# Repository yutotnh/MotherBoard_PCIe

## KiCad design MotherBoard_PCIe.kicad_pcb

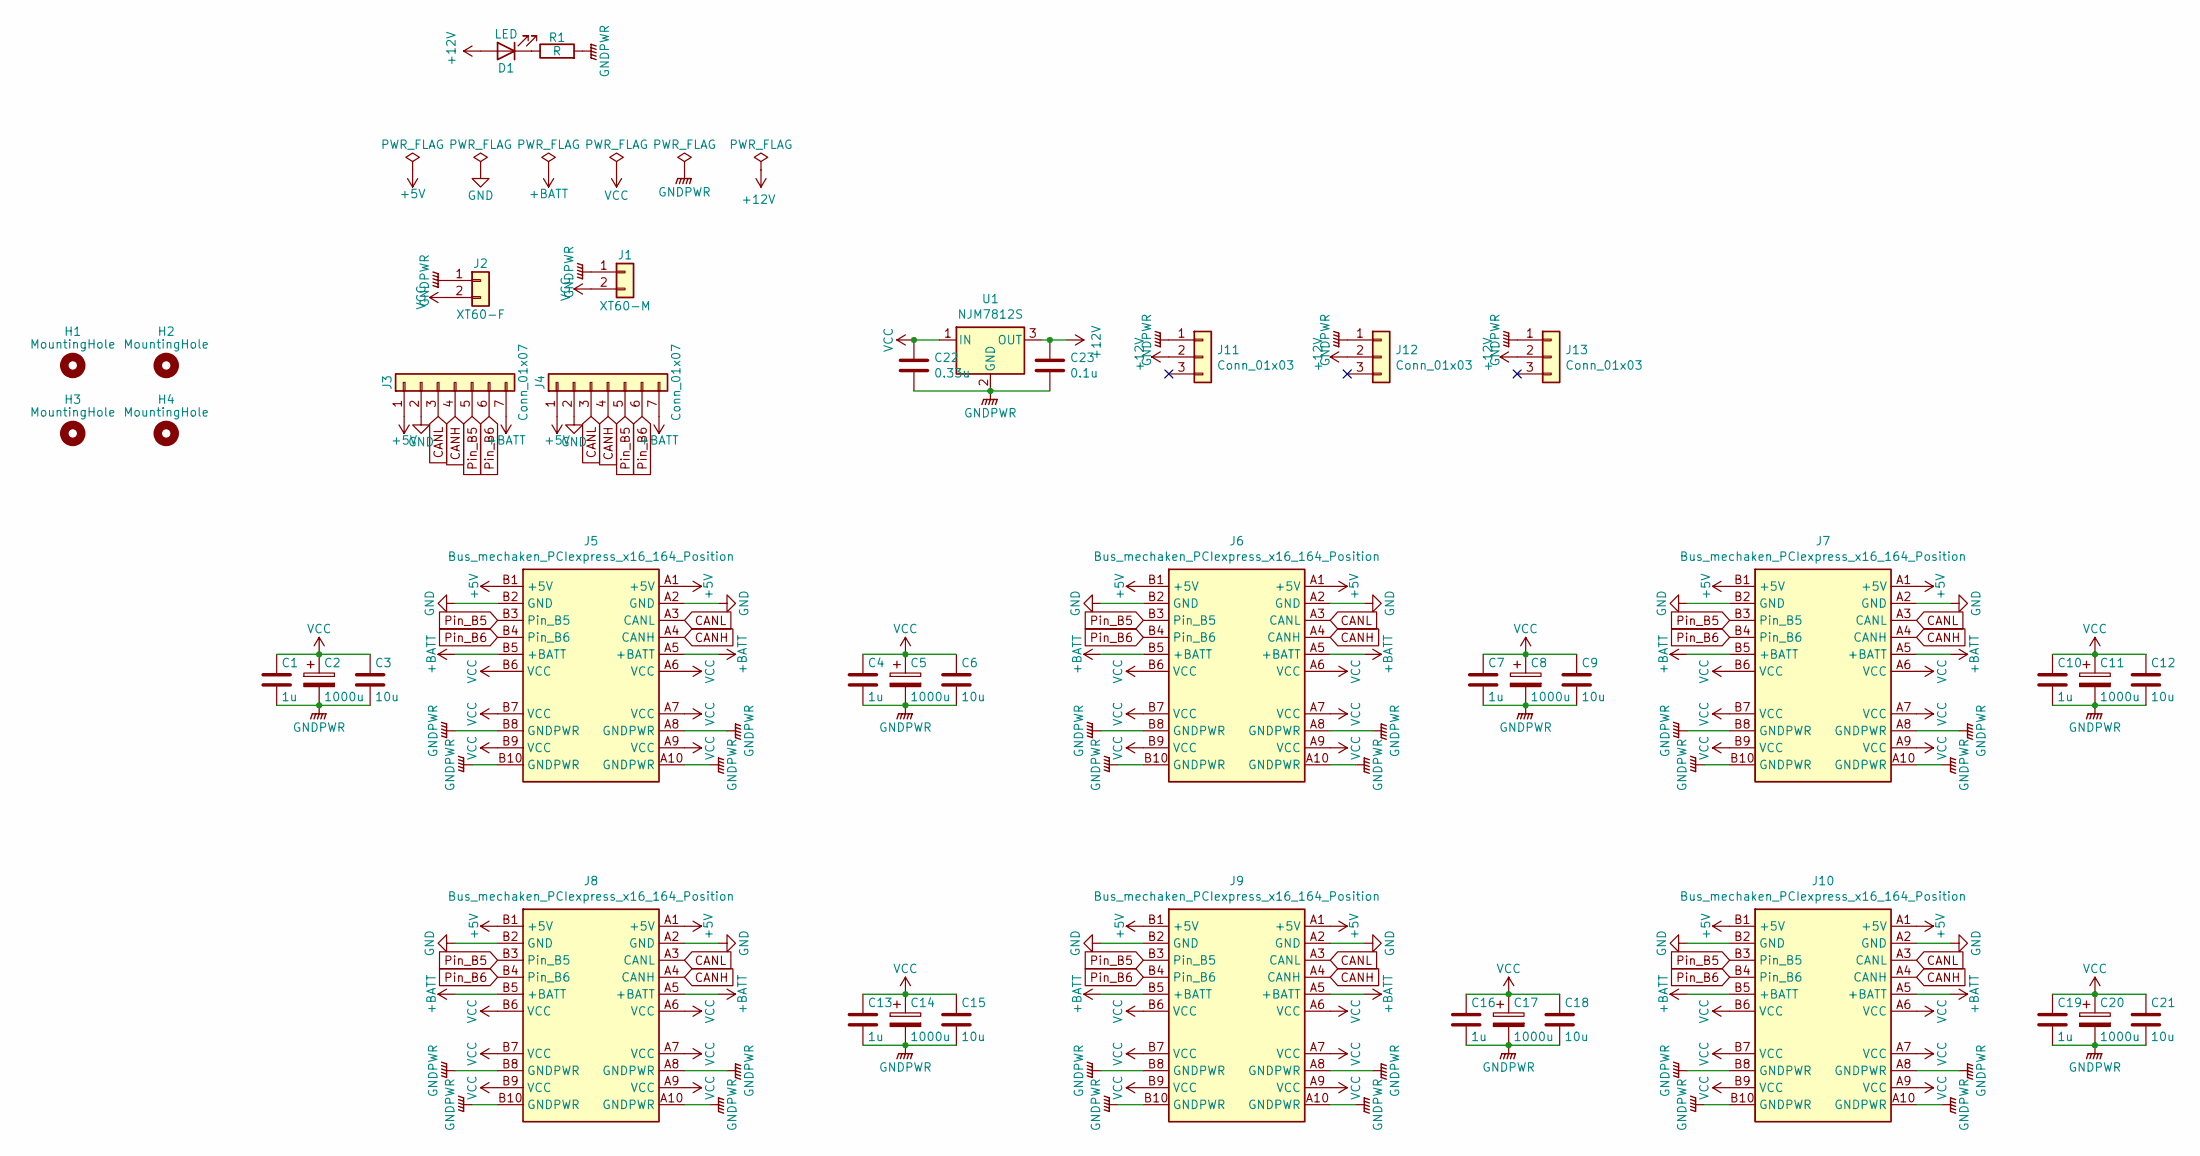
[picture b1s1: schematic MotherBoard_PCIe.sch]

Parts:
C1, C4, C7, C10, C13, C16, C19: 1u; C_0805_2012Metric
C2, C5, C8, C11, C14, C17, C20: 1000u; CP_Radial_D12.5mm_P5.00mm
C3, C6, C9, C12, C15, C18, C21: 10u; C_0805_2012Metric
C22: 0.33u; C_0805_2012Metric
C23: 0.1u; C_0805_2012Metric
D1: LED; LED_D4.0mm
H1, H2, H3, H4: MountingHole; MountingHole_3.2mm_M3
J1: XT60-M; AMASS_XT60-M_1x02_P7.20mm_Vertical
J2: XT60-F; AMASS_XT60-F_1x02_P7.20mm_Vertical
J3, J4: Conn_01x07; PinHeader_1x07_P2.54mm_Vertical
J5, J6, J7, J8, J9, J10: Bus_mechaken_PCIexpress_x16_164_Position; Socket_mechaken_PCIexpress_x16_164_position
J11, J12, J13: Conn_01x03; FanPinHeader_1x03_P2.54mm_Vertical
R1: R; R_0603_1608Metric_Pad1.05x0.95mm_HandSolder
U1: NJM7812S; TO-252-2

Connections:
+5V: J3.1, J4.1, J5.A1 (+5V), J5.B1 (+5V), J6.A1 (+5V), J6.B1 (+5V), J7.A1 (+5V), J7.B1 (+5V), J8.A1 (+5V), J8.B1 (+5V), J9.A1 (+5V), J9.B1 (+5V), J10.A1 (+5V), J10.B1 (+5V)
+12V: C23.1, D1.2 (A), J11.2, J12.2, J13.2, U1.3 (OUT)
+BATT: J3.7, J4.7, J5.A5 (+BATT), J5.B5 (+BATT), J6.A5 (+BATT), J6.B5 (+BATT), J7.A5 (+BATT), J7.B5 (+BATT), J8.A5 (+BATT), J8.B5 (+BATT), J9.A5 (+BATT), J9.B5 (+BATT), J10.A5 (+BATT), J10.B5 (+BATT)
CANH: J3.4, J4.4, J5.A4 (CANH), J6.A4 (CANH), J7.A4 (CANH), J8.A4 (CANH), J9.A4 (CANH), J10.A4 (CANH)
CANL: J3.3, J4.3, J5.A3 (CANL), J6.A3 (CANL), J7.A3 (CANL), J8.A3 (CANL), J9.A3 (CANL), J10.A3 (CANL)
GND: J3.2, J4.2, J5.A2 (GND), J5.B2 (GND), J6.A2 (GND), J6.B2 (GND), J7.A2 (GND), J7.B2 (GND), J8.A2 (GND), J8.B2 (GND), J9.A2 (GND), J9.B2 (GND), J10.A2 (GND), J10.B2 (GND)
GNDPWR: C1.2, C2.2, C3.2, C4.2, C5.2, C6.2, C7.2, C8.2, C9.2, C10.2, C11.2, C12.2, C13.2, C14.2, C15.2, C16.2, C17.2, C18.2, C19.2, C20.2, C21.2, C22.2, C23.2, J1.1, J2.1, J5.A8 (GNDPWR), J5.A10 (GNDPWR), J5.B8 (GNDPWR), J5.B10 (GNDPWR), J6.A8 (GNDPWR), J6.A10 (GNDPWR), J6.B8 (GNDPWR), J6.B10 (GNDPWR), J7.A8 (GNDPWR), J7.A10 (GNDPWR), J7.B8 (GNDPWR), J7.B10 (GNDPWR), J8.A8 (GNDPWR), J8.A10 (GNDPWR), J8.B8 (GNDPWR), J8.B10 (GNDPWR), J9.A8 (GNDPWR), J9.A10 (GNDPWR), J9.B8 (GNDPWR), J9.B10 (GNDPWR), J10.A8 (GNDPWR), J10.A10 (GNDPWR), J10.B8 (GNDPWR), J10.B10 (GNDPWR), J11.1, J12.1, J13.1, R1.2, U1.2 (GND)
unnamed: D1.1 (K), R1.1
Pin_B5: J3.5, J4.5, J5.B3 (Pin_B5), J6.B3 (Pin_B5), J7.B3 (Pin_B5), J8.B3 (Pin_B5), J9.B3 (Pin_B5), J10.B3 (Pin_B5)
Pin_B6: J3.6, J4.6, J5.B4 (Pin_B6), J6.B4 (Pin_B6), J7.B4 (Pin_B6), J8.B4 (Pin_B6), J9.B4 (Pin_B6), J10.B4 (Pin_B6)
VCC: C1.1, C2.1, C3.1, C4.1, C5.1, C6.1, C7.1, C8.1, C9.1, C10.1, C11.1, C12.1, C13.1, C14.1, C15.1, C16.1, C17.1, C18.1, C19.1, C20.1, C21.1, C22.1, J1.2, J2.2, J5.A6 (VCC), J5.A7 (VCC), J5.A9 (VCC), J5.B6 (VCC), J5.B7 (VCC), J5.B9 (VCC), J6.A6 (VCC), J6.A7 (VCC), J6.A9 (VCC), J6.B6 (VCC), J6.B7 (VCC), J6.B9 (VCC), J7.A6 (VCC), J7.A7 (VCC), J7.A9 (VCC), J7.B6 (VCC), J7.B7 (VCC), J7.B9 (VCC), J8.A6 (VCC), J8.A7 (VCC), J8.A9 (VCC), J8.B6 (VCC), J8.B7 (VCC), J8.B9 (VCC), J9.A6 (VCC), J9.A7 (VCC), J9.A9 (VCC), J9.B6 (VCC), J9.B7 (VCC), J9.B9 (VCC), J10.A6 (VCC), J10.A7 (VCC), J10.A9 (VCC), J10.B6 (VCC), J10.B7 (VCC), J10.B9 (VCC), U1.1 (IN)

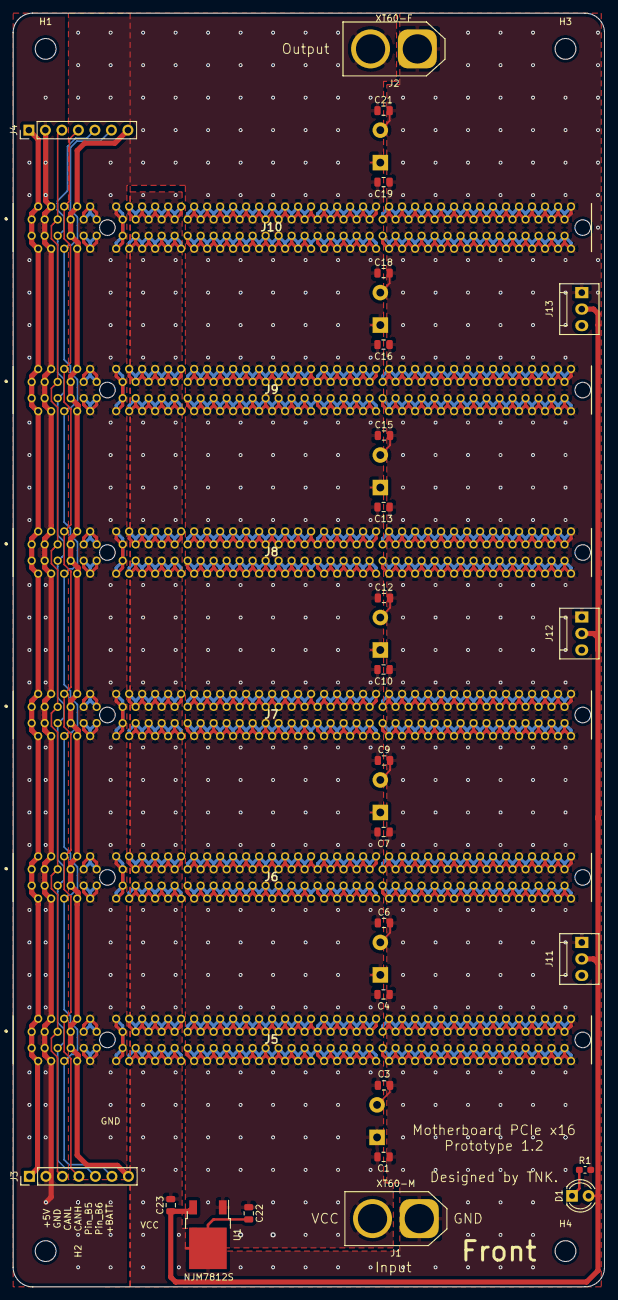
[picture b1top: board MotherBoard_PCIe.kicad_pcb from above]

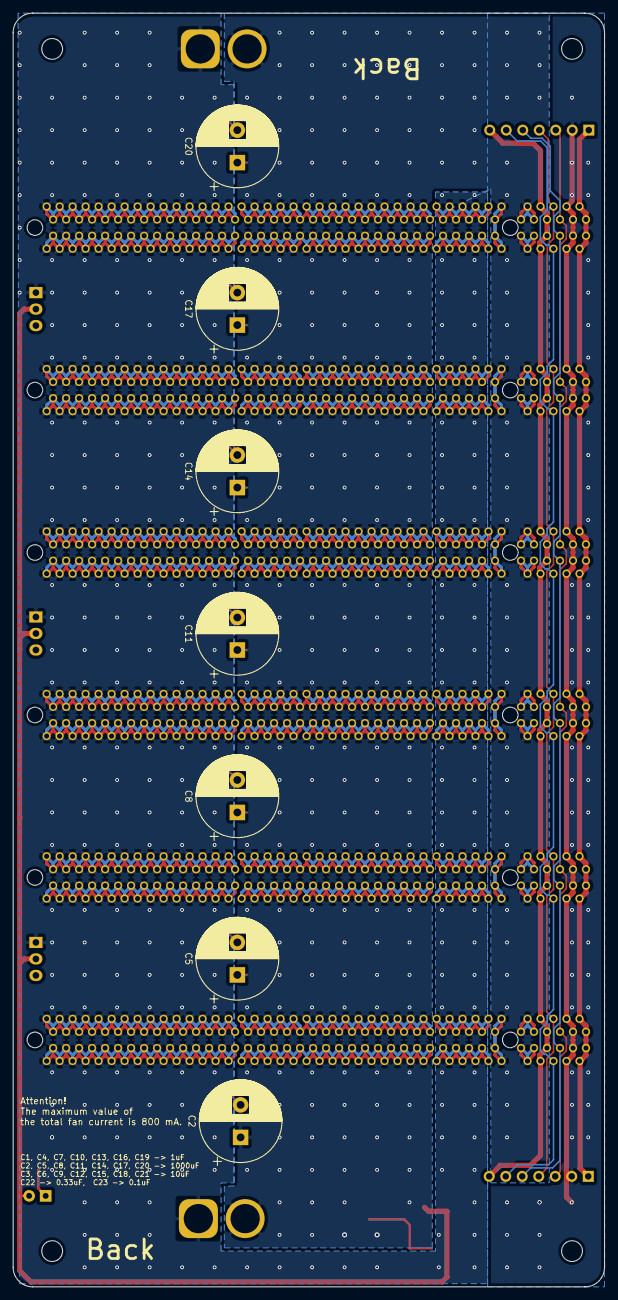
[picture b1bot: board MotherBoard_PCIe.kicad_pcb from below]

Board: 2 copper layers, 91.0 x 196.0 mm, 43 parts (7 on the bottom side), 11 nets.

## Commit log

2019-11-29 Prototype 1.0
2019-11-29 +Battery Strong
2020-01-29 buck-up
2020-01-29 change
    おおよその部品の配置を開始
2020-01-30 add
    いったん完成
2020-01-30 add
    3ピンファンコネクタを追加
2020-01-30 clean
2020-02-01 add
    通電確認用LEDとファンコネクタを1つ追加
2020-02-02 change
    フットプリントのリファレンスを変更したのを適応
2020-02-02 create
2020-02-16 clean
    PCIeソケットの3Dデータを変更
2020-02-16 add
    step file
2020-03-02 fix
    セラミックコンデンサのシルクが電解コンデンサのパッドと一部かぶっていたのを修正
2020-06-21 fix
    H4にM3ねじを使ったらビアから導通しそうだったので修正
2020-06-21 change
    シルク印刷の修正（githubのリンク等）
2020-06-21 add
    gitignoreを追加
2020-06-21 .gitignore is now working
2021-09-24 Create LICENSE
